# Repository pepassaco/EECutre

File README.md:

# EECutre
Electroencephalography made cheap and easy

Project base on the INA163 instrumentation amplifier for the readout of encephalographic signals

The overall cost of one device (including the INA163 and three electrodes) should be under 50€ (updated 06/2022) (yes, Aliexpress is your friend). It is also easy to build (it only requires basic soldering skills) and does not require neither special power supply nor other electronics instrumentation for it to work

## Materials needed

- The designed PCB (schematics in this repo)
- Two 7V-12V batteries
- Electrodes (highly recommended use of either silver or gold-plated electrodes)
- 3,5mm male to male audio cable
- A PC running Matlab (Maybe python in a future, who knows) with 3,5mm mic input
- Conductive gel

## PCB construction

Just solder the SMD components as shown in the schematic. It is highly recommended to use a stencil with solder paste. Nevertheless, the components are big enough (0603) for allowing a painless hand-soldering experience. 

## Usage

**IMPORTANT:** for safety issues, it is recommended to run this program from a laptop computer not connected to the plug of your house. I mean, this is as risky as wearing some wired headsets, but everyone warns about this online, so here I am. I'm not responsible for anything, u know.

**Note:** This is not an easy project for plug-n-play users. The amplifiers are highly sensitive to noise and you will surely have to debug the system in order to obtain optimal performance. In this way, I highly recommend reading some papers about how EEG really work in order to fully understand what we are trying to achieve. As a first reference, I can recommend the following video: 

[An introduction to EEG](https://www.youtube.com/watch?v=XMizSSOejg0)

#### Connection of electrodes

The connection of the electrodes can be carried out in multiple different ways. It will all depend on how many electrodes you have and what signals you want to measure. Moreover, since we are using differential amplifiers, the signal will be measured between the difference of two point, so that there will be no absolute ground. This way, you will have to decide what electrode to compare with which one in order to see the signal you are looking for. See the following great video in order to understand the different usual montages: 

[EEG Montages](https://www.youtube.com/watch?v=AcW97nMLGEs)

As a first approach, using two electrodes for measuring the left and right halfs of the frontal lobe and a third electrode as a wirtual ground behind your ear can be a good solution for measuring alfa waves and eye blinks. 

Remeber to apply conductive gel between the electrode and the skull and to get the electrodes as fixed to the head as possible without hurting the patient, since loose electrodes can lead to noise in the measurements 

#### The PCB

The PCB is powered though two batteries (between 7V and 12V each) so that the operational amplifiers can work with both positive and negative voltages.

Connect the electrodes to the PCB and the PCB to the audio input of your laptop. Beware that this board is extremely noise sensitive, so stay away from low-frequency EMI sources. Also, always power it through batteries, since the 50Hz/60Hz of a power supply can dirty the ignal output

#### The software

Cuando tenga tiempo escribo algo wapo, primero tengo que mriar si funciona

## Other uses

Due to the high sensibility of the devide, the EECutre may also be used for readout of Electrocardiographic signals as well as Electromipgraphic signals. Just connect different electrodes to the input ports of the PCB and have fun!

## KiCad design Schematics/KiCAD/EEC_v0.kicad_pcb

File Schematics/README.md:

### Structure: 

- KiCAD: KiCAD Project
- Gerbers: Gerber and drill files for directly manufacturing the PCBs
- schematic_vXX.pdf: PDF version of the circuit diagram

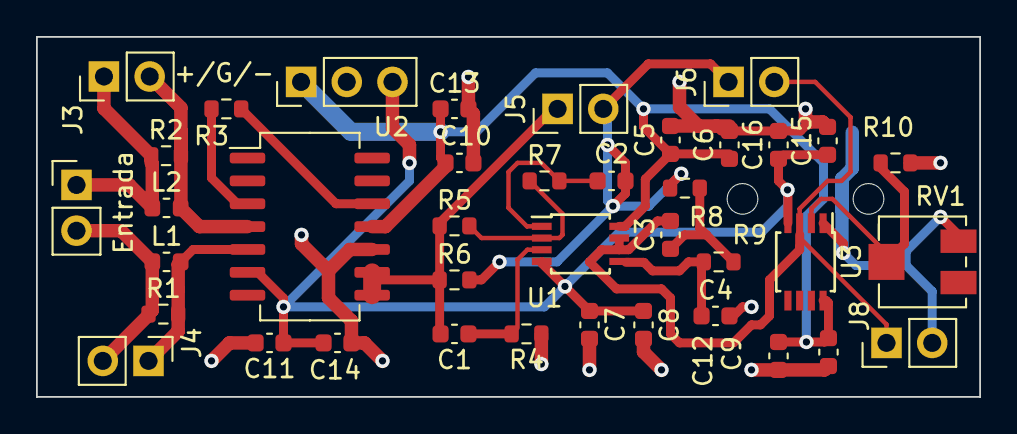
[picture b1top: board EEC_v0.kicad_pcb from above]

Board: 2 copper layers, 52.4 x 20.0 mm, 40 parts (1 on the bottom side), 19 nets.

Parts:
+/G/-: Alimentación; PinHeader_1x03_P2.54mm_Vertical
C1, C2: 1.6uF; C_0603_1608Metric
C3, C4: 2.7uF; C_0603_1608Metric
C5, C7, C9, C10, C11, C15: 100nF; C_0603_1608Metric
C6, C8, C12, C13, C14, C16: 1uF; C_0603_1608Metric
Entrada: Entrada; PinHeader_1x02_P2.54mm_Vertical
J3: Jumper V-; PinHeader_1x02_P2.54mm_Vertical
J4: Jumper V+; PinHeader_1x02_P2.54mm_Vertical
J5: Jumper Notch; PinHeader_1x02_P2.54mm_Vertical
J6: Jumper Paso Bajo; PinHeader_1x02_P2.54mm_Vertical
J8: Jumper Amplificador; PinHeader_1x02_P2.54mm_Vertical
L1, L2: 1.2uH; L_0603_1608Metric
R1, R2: 47R; R_0603_1608Metric
R3: 56R; R_0603_1608Metric
R4, R5, R6, R7: 2K; R_0603_1608Metric
R8, R9: 1.5K; R_0603_1608Metric
R10: 1K; R_0603_1608Metric
RV1: 50K; Potentiometer_Bourns_3214J_Horizontal
Salida: AudioJack3; Jack_3.5mm_CUI_SJ-3523-SMT_Horizontal
U1, U3: LM358; TSSOP-8_3x3mm_P0.65mm
U2: INA163UA; SO-14_5.3x10.2mm_P1.27mm

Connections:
+VDC: +/G/-.1, C5.1, C6.1, C9.1, C10.1, C12.1, C13.1, U1.8 (V+), U2.11 (V+), U3.8 (V+)
-VDC: +/G/-.3, C7.1, C8.1, C11.1, C14.1, C15.1, C16.1, U1.4 (V-), U2.6 (V-), U3.4 (V-)
/Ganancia: R3.1, U2.12 (GS2)
/Sense: C1.2, J5.1, R5.1, R6.1, U2.8 (SENSE), U2.9 (VO)
Earth: +/G/-.2, C4.2, C5.2, C6.2, C7.2, C8.2, C9.2, C10.2, C11.2, C12.2, C13.2, C14.2, C15.2, C16.2, R4.1, R10.2, Salida.T, U2.10 (REF)
unnamed: C1.1, R4.2, U1.3 (+)
unnamed: C2.1, R7.2, U1.1
unnamed: C2.2, J5.2, J6.1, R6.2, R8.1
unnamed: C3.1, R8.2, R9.1
unnamed: C3.2, J6.2, J8.1, U1.6 (-), U1.7, U3.3 (+)
unnamed: C4.1, R9.2, U1.5 (+)
unnamed: Entrada.1, J3.1, L2.1, R2.1
unnamed: Entrada.2, J4.2, L1.1, R1.1
unnamed: J3.2, L2.2, R2.2, U2.4 (VIN-)
unnamed: J4.1, L1.2, R1.2, U2.5 (VIN+)
unnamed: J8.2, RV1.1, Salida.R, Salida.S, U3.1
unnamed: R3.2, U2.3 (GS1)
unnamed: R5.2, R7.1, U1.2 (-)
unnamed: R10.1, RV1.2, U3.2 (-)

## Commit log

2023-04-02 New version (see changelog)
2023-04-02 Revert "V2.0"
